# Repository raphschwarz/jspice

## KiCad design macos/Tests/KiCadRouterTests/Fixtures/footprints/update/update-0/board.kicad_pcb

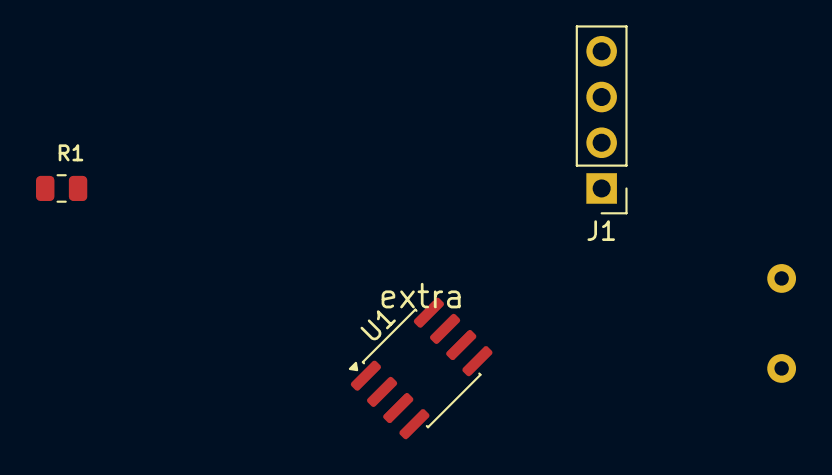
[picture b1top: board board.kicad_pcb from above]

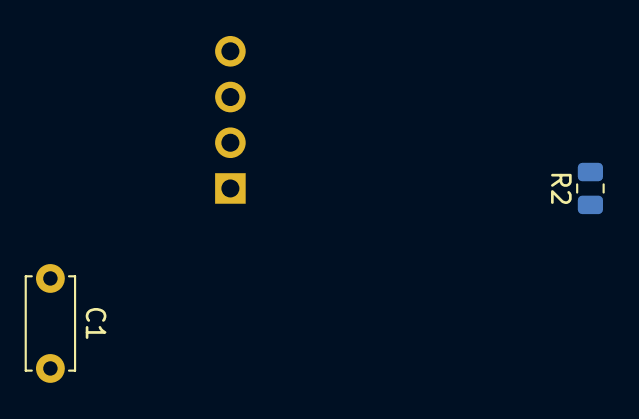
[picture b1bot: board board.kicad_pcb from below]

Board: 2 copper layers, 5 parts (2 on the bottom side), 2 nets, no tracks yet.

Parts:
C1: 100n; C_Disc_D5.0mm_W2.5mm_P5.00mm
J1: Conn_01x04; PinHeader_1x04_P2.54mm_Vertical
R1: 10k; R_0805_2012Metric
R2: R_0805_2012Metric
U1: LM358; SOIC-8_3.9x4.9mm_P1.27mm

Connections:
GND: R1.1, U1.2
VCC: R1.2 (B), U1.3

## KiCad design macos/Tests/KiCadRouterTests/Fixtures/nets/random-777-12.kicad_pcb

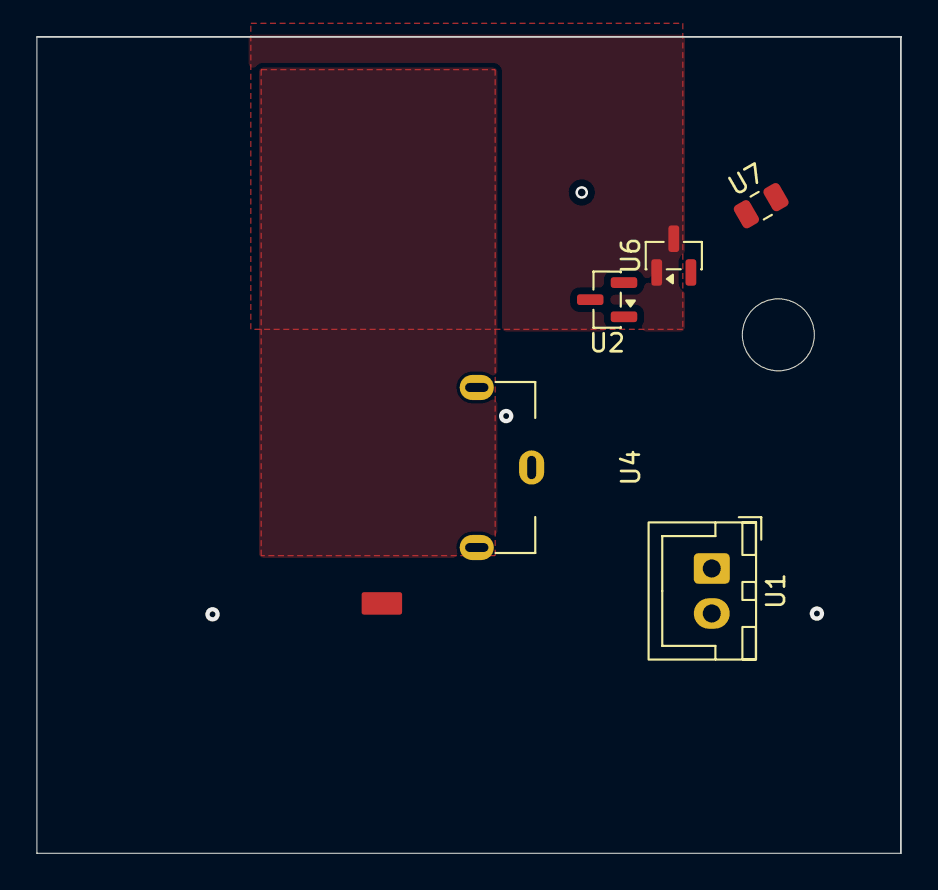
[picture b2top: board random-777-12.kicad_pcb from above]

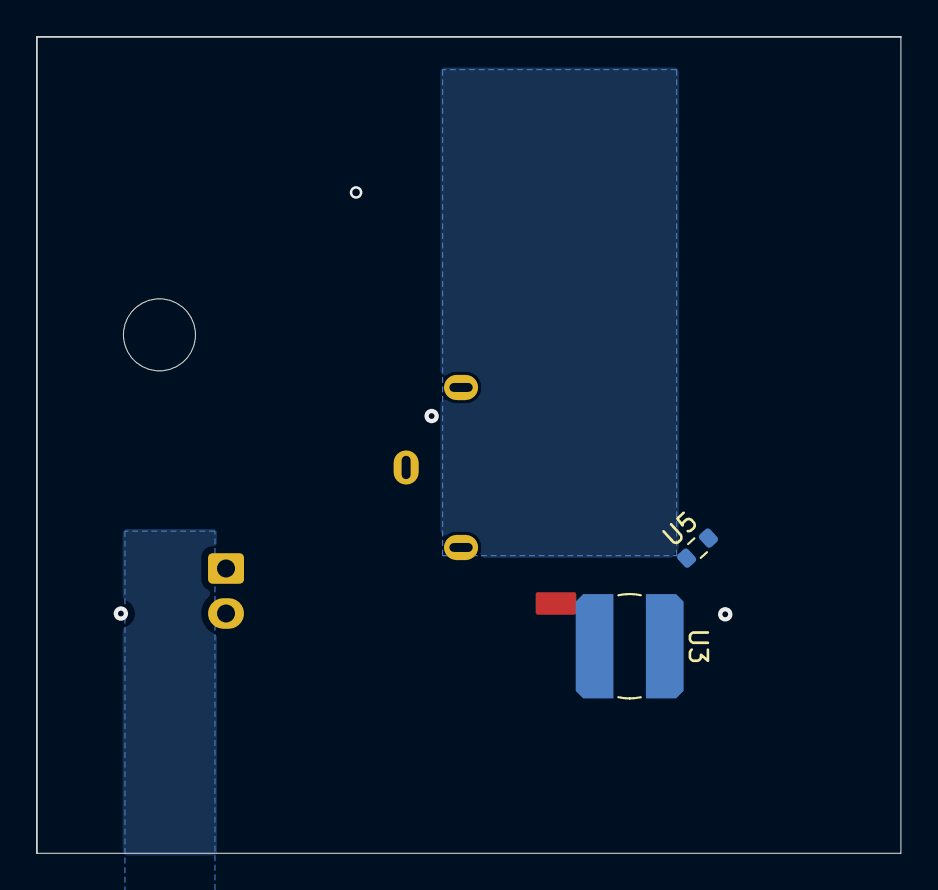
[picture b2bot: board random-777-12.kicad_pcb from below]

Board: 2 copper layers, 48.0 x 45.4 mm, 7 parts (2 on the bottom side), 4 nets, no tracks yet.

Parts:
U1: JST_XH_B2B-XH-A_1x02_P2.50mm_Vertical
U2, U6: SOT-23
U3: L_Bourns_SDR0604
U4: BatteryHolder_Keystone_590
U5: R_0603_1608Metric
U7: C_0805_2012Metric

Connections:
/net3: U1.2, U5.2, U6.1
D7: U3.1, U7.2
D12: U2.3, U7.1
VCC: U2.1, U2.2

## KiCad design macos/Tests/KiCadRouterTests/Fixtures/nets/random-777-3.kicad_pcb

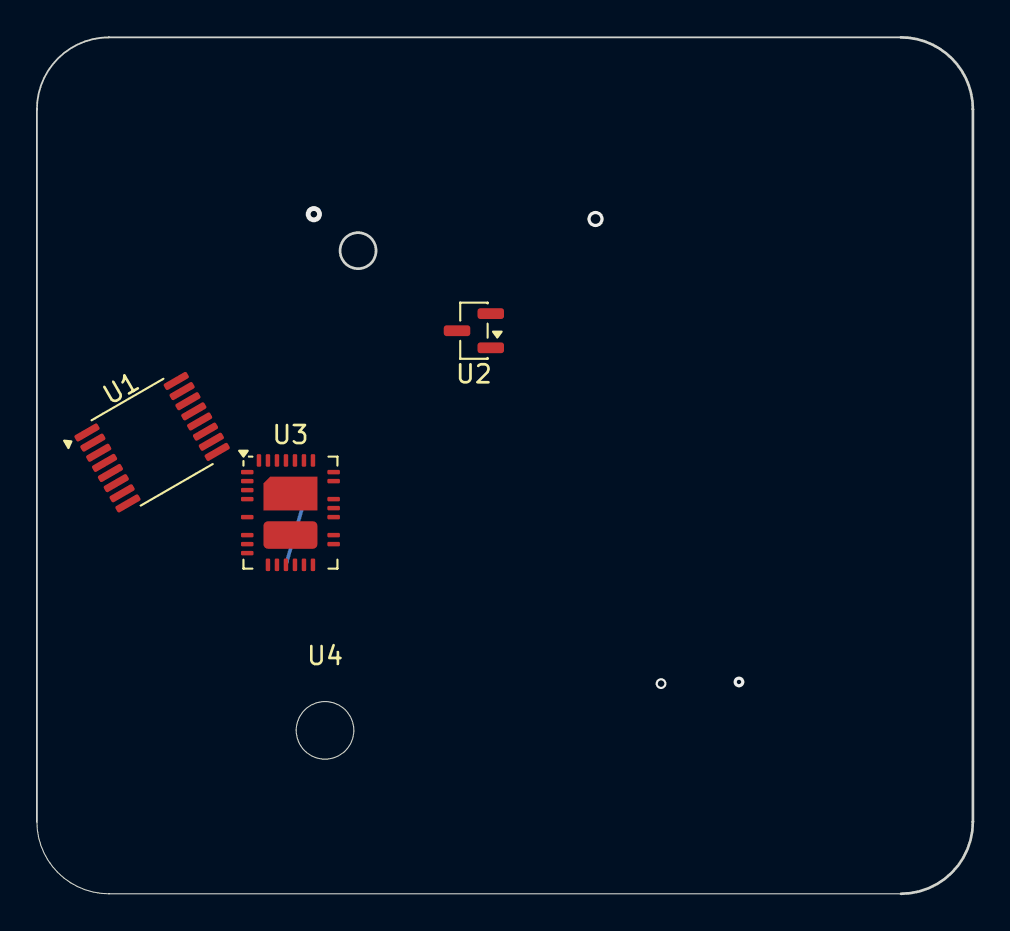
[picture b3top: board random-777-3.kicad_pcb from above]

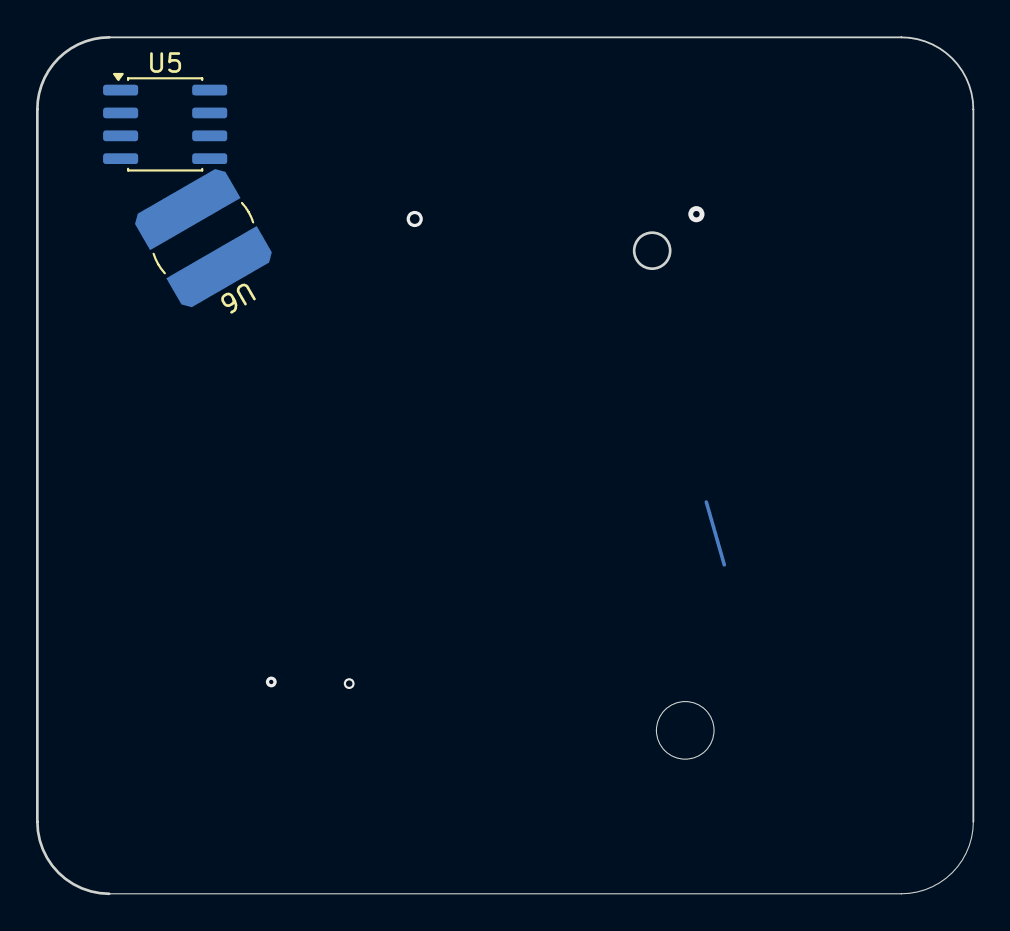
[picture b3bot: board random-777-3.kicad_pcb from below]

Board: 4 copper layers, 52.0 x 47.6 mm, 6 parts (2 on the bottom side), 5 nets.

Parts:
U1: TSSOP-16_4.4x5mm_P0.65mm
U2: SOT-23
U3: Analog_QFN-28-36-2EP_5x6mm_P0.5mm
U4: MountingHole_3.2mm_M3
U5: SOIC-8_3.9x4.9mm_P1.27mm
U6: L_Bourns_SDR0604

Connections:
/net3: U1.1, U1.4, U2.3, U3.1, U3.6, U3.12, U3.16, U3.31, U3.35, U5.2, U5.8
/sub/clk: U1.11, U3.20, U3.21, U3.28, U5.4
N1: U1.3, U1.7, U1.14, U2.1, U3.3, U3.27
N2: U1.6, U1.8, U1.10, U2.2, U3.4, U3.15, U3.32, U3.36, U3.37, U5.7, U6.1
SIG1: U1.9, U1.15, U3.8, U3.9, U3.25, U5.3, U5.6

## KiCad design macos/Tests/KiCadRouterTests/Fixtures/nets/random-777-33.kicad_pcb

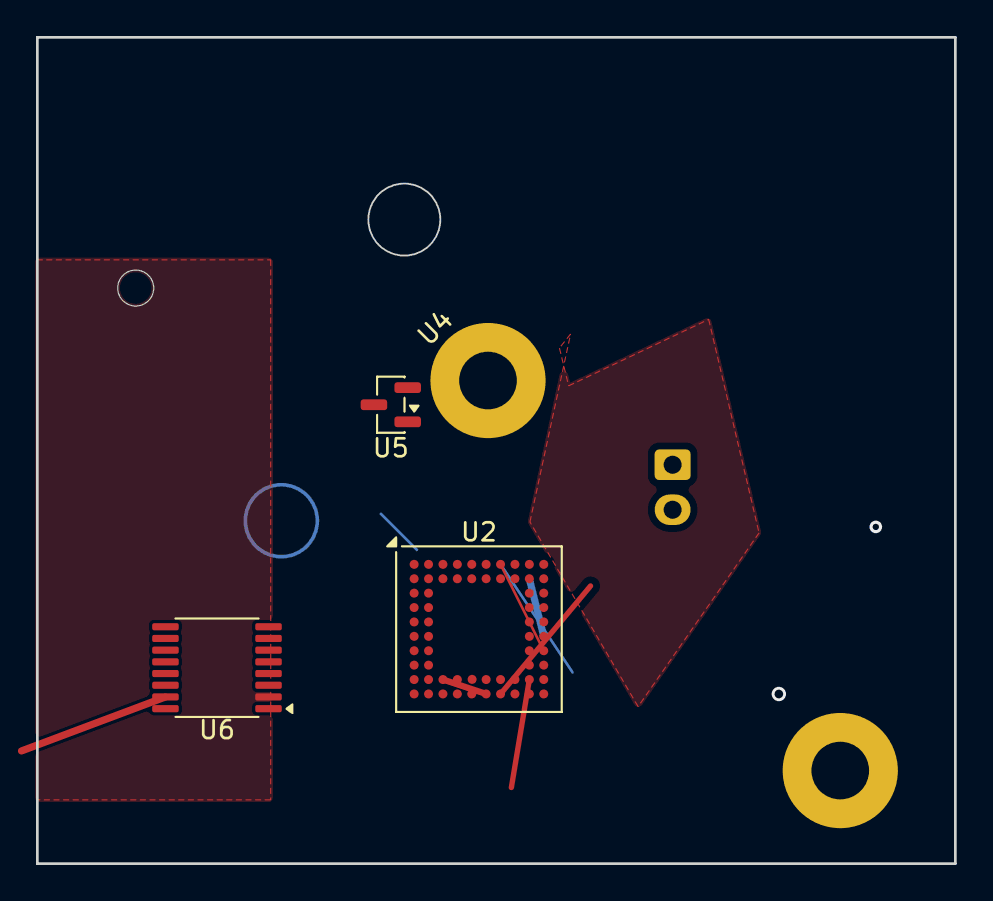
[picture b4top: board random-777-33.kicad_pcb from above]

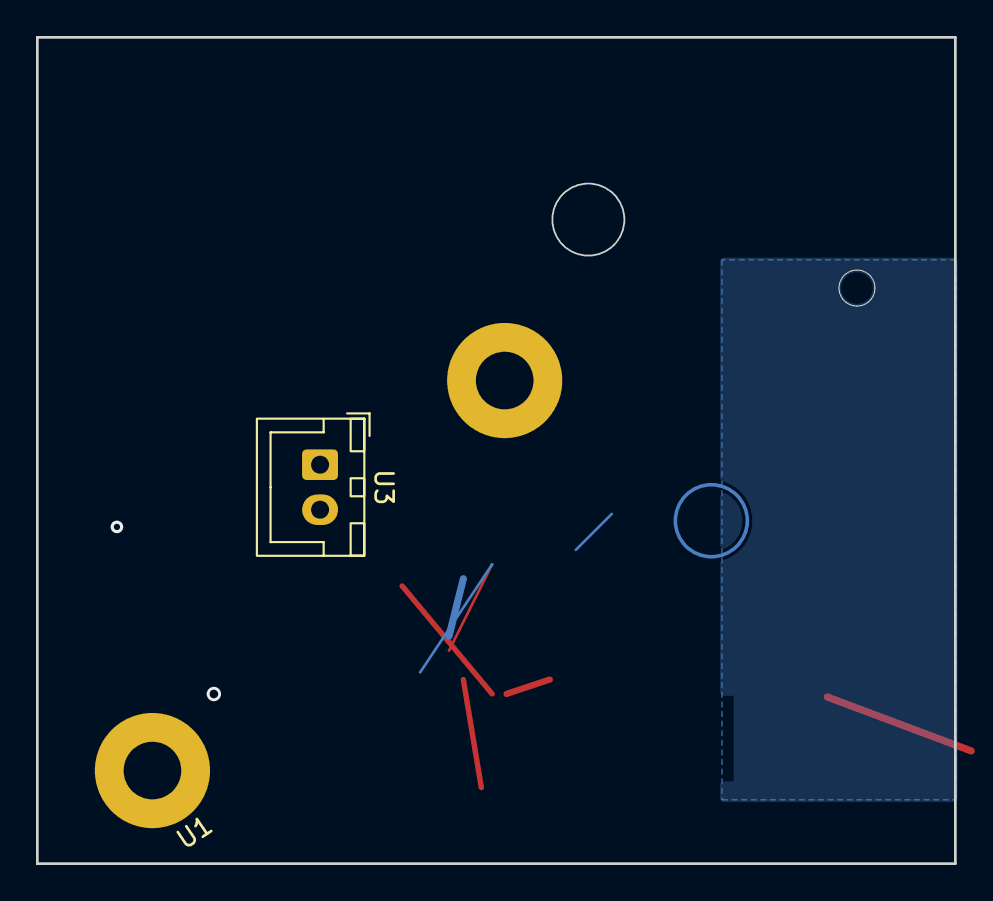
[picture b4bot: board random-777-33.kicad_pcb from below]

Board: 2 copper layers, 51.0 x 45.9 mm, 6 parts (2 on the bottom side), 12 nets.

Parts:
U1, U4: MountingHole_3.2mm_M3_Pad
U2: BGA-64_9.0x9.0mm_Layout10x10_P0.8mm
U3: JST_XH_B2B-XH-A_1x02_P2.50mm_Vertical
U5: SOT-23
U6: TSSOP-16_4.4x5mm_P0.65mm

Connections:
/net3: U2.A4, U2.C2, U6.1
/sub/clk: U2.D2, U2.E10, U2.H10, U2.K2, U2.K4, U4.1
D7: U2.F1, U2.H9, U2.K1, U2.K8
D12: U2.H1, U2.J1, U6.3, U6.15
GND: U2.A3, U2.J2, U2.J8, U2.K3, U2.K6, U2.K7, U5.2, U6.5
N1: U2.A1, U2.A7, U2.A9, U2.B7, U2.B10, U2.H2, U2.J6, U6.9, U6.10
N2: U2.B3, U2.F2, U3.1, U6.11, U6.16
N3: U2.A10, U2.B9, U6.12, U6.13
PWR1: U1.1, U2.C10, U2.D9, U2.J5, U2.K5
PWR_5V: U2.A5, U2.B2, U2.K9, U2.K10, U6.2
SIG1: U2.A8, U2.D10, U2.G2, U2.J3, U3.2, U6.4, U6.7, U6.8
SIG2: U2.D1, U2.E1, U2.E9, U2.J7, U5.3
